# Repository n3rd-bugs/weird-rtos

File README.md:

Weird RTOS
==========
This is an educational RTOS that can be used with medium ended micro-controllers including 8-bit AVRs and Cortex-M3/4.

## Features
- Highly scalable for number of small to medium scale applications
- Priority based aperiodic scheduler
- Dynamic task creation and deletion
- *Condition* to create application specific signaling mechanisms like timers, events etc.
- *Semaphore* with optional specific interrupt protection
- *File system* based pipes to support data queues
- Support for suspending a single task on multiple conditions to eliminate multiple tasks
- A small networking stack with IPv4, ARP, UDP, TCP
- Support for idle work to offload low priority work from main tasks

## Supported MCUs and Platforms
| MCU/Platform | Core | RTOS Features |
| ------------ | ---- | -------- |
| atmega644 | AVR 8-bit | USART, ADC, SPI, Ethernet, MMC, File system, Alphanumeric LCD |
| atmega1284 | AVR 8-bit | USART, ADC, SPI, Ethernet, MMC, File system, Alphanumeric LCD |
| STM32F407vgt6 | Cortex-M4 | USART, SPI, Ethernet |
| STM32F103-stamp | Cortex-M3 | USART, ADC, SPI, Ethernet, MMC, File system, Alpha Numeric LCD |

## Minimum Requirements
| Controller | ROM | ROM actual\* | RAM | RAM Actual\*\* |
| ---------- | --- | ---------- | --- | ---------- |
| AVR 8-bit | 4 KB | 3086 bytes | 1 KB | 345 bytes |
| Cortex-M3 | 4 KB | 2075 bytes | 2 KB | 784 bytes |
| Cortex-M4 | 4 KB | 2139 bytes | 2 KB | 960 bytes |

_* with size optimizations_
_** hello.c example with serial disabled, not including system stack_

## Building
### Building as Library
To build the RTOS as library follow these steps:
1. Create a build folder
    `mkdir lib-build`
    `cd lib-build`
2. Configure the library project for a platform
    `cmake -G "Unix Makefiles" -DCMAKE_TOOLCHAIN_FILE=<path-to-root>/cmake/toolchains/<cross-tool>.cmake <path-to-root>`
3. Build the library
    `make`

The created library can be used to build sample applications using other tools.

### Building a Sample
To build an example project please follow these steps:
1. Create a build folder
    `mkdir build`
    `cd build`
2. Configure the example project for a platform
    `cmake -G "Unix Makefiles" -DCMAKE_TOOLCHAIN_FILE=<path-to-root>/cmake/toolchains/<cross-tool>.cmake <path-to-root>/examples/<example>`
3. Build the sample
    `make`

## Configurations
Weird-RTOS provides various configuration options that can be best viewed if project is configured through cmake-gui. These allow user to adjust various RTOS features according to his requirements.

## Source Organization

```
+-- 3rdparty - 3rd party components
+-- api - Higher level components including TFTP, weird-view IoT framework
+-- cmake - Cmake project files
|   +-- modules - Implements various helper APIs for cmake
|   +-- toolchains - Provides toolchain files
+-- docs - Related documentation
+-- examples - Some usage examples
+-- port - Target specific bits
|   +-- kernel - Target specific kernel components
|   +-- target - Platform specific device drivers
|       +-- <platform> - A platform entry
|           +-- board - Board specific configurations
|           +-- io - Device drivers
|           +-- schematics - Platform schematics if applicable
|           +-- utils - Broad utilities
|   +-- toolset - Toolset specific definitions
+-- rtos - Operating system generic components
|   +-- fs - File system
|   +-- io - IO device drivers and their middleware
|   +-- mem - Memory management
|   +-- net - Networking stack
|   +-- kernel - Kernel APIs
|   +-- utils - System utilities
```

## Documentation
### Kernel
- [Scheduler](docs/kernel/SCHEDULER.md)
- [Semaphore](docs/kernel/SEMAPHORE.md)
- [Sleep](docs/kernel/SLEEP.md)
- [Idle](docs/kernel/IDLE.md)
- [System Logging](docs/kernel/LOGGING.md)

## Licensing
This is a _non-commercial_ RTOS, for more details see [License Agreement](LICENSE.md).

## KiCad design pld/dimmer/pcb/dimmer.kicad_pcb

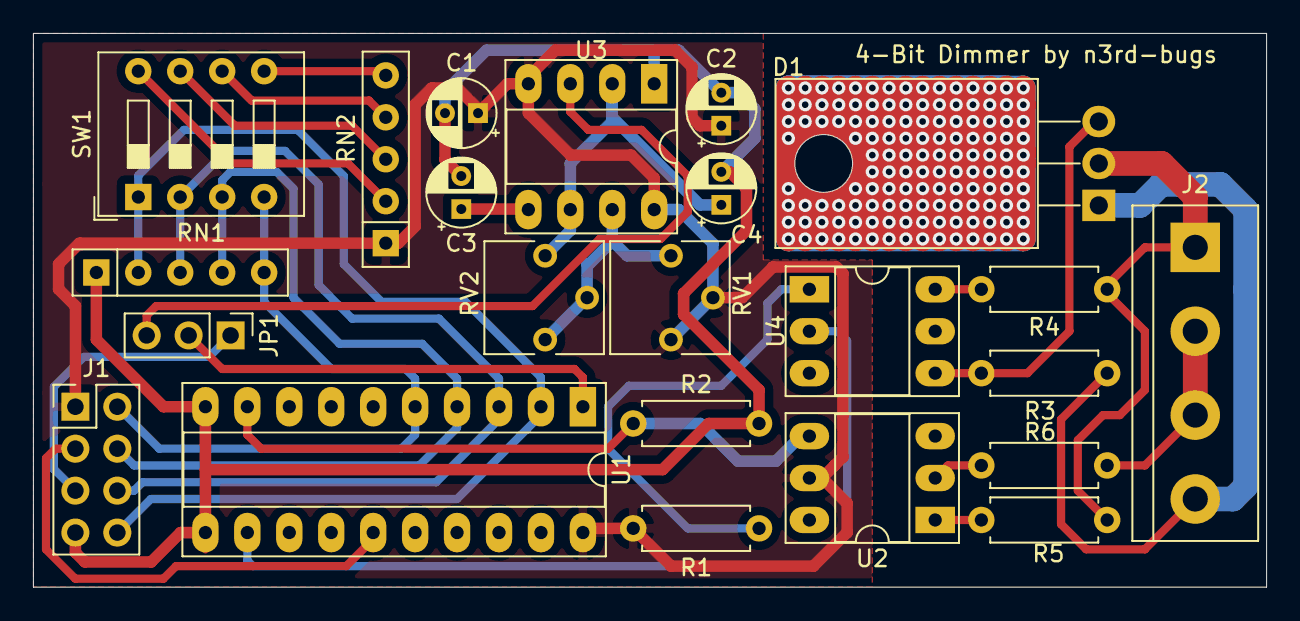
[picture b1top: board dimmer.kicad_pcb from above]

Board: 2 copper layers, 74.7 x 33.5 mm, 23 parts (0 on the bottom side), 27 nets.

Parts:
C1: .01u; CP_Radial_D4.0mm_P2.00mm
C2: 10u; CP_Radial_D4.0mm_P2.00mm
C3: 0.01u; CP_Radial_D4.0mm_P2.00mm
C4: ,1u; CP_Radial_D4.0mm_P2.00mm
D1: BTA20; TO-220-3_Horizontal_TabDown
J1: MCU; PinHeader_2x04_P2.54mm_Vertical
J2: AC/Load; TerminalBlock_bornier-4_P5.08mm
JP1: Jumper_3_Open; PinHeader_1x03_P2.54mm_Vertical
R1: 1k; R_Axial_DIN0207_L6.3mm_D2.5mm_P7.62mm_Horizontal
R2: 10k; R_Axial_DIN0207_L6.3mm_D2.5mm_P7.62mm_Horizontal
R3, R4: 100R; R_Axial_DIN0207_L6.3mm_D2.5mm_P7.62mm_Horizontal
R5, R6: 100k; R_Axial_DIN0207_L6.3mm_D2.5mm_P7.62mm_Horizontal
RN1: 10K; R_Array_SIP5
RN2: 100R; R_Array_SIP5
RV1, RV2: 10k; Potentiometer_Vishay_T73YP_Vertical
SW1: PWM; SW_DIP_SPSTx04_Slide_9.78x12.34mm_W7.62mm_P2.54mm
U1: GAL16V8; DIP-20_W7.62mm_Socket_LongPads
U2: 4N35; DIP-6_W7.62mm_Socket_LongPads
U3: LM555; DIP-8_W7.62mm_Socket_LongPads
U4: MOC3052M; DIP-6_W7.62mm_Socket_LongPads

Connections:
+5V: C1.1, C2.1, J1.1, R1.2, RN2.1, RV1.1, RV1.2, U1.20, U2.5, U3.4, U3.8
CLK: JP1.2, U1.1
CLK555: JP1.3, U3.3
CLKMCU: J1.5, JP1.1
GNDD: C1.2, C2.2, C3.2, C4.2, J1.7, R2.2, RN1.1, U1.10, U1.11, U3.1
IN-0: J1.8, RN1.2, SW1.1, U1.2
IN-1: J1.6, RN1.3, SW1.2, U1.3
IN-2: J1.4, RN1.4, SW1.3, U1.4
IN-3: J1.2, RN1.5, SW1.4, U1.5
LINEINV: J1.3, U1.15
Line: R2.1, U1.9, U2.4
unnamed: C3.1, U3.5
unnamed: C4.1, RV2.3, U3.2, U3.6
unnamed: D1.1, J2.4, R3.2
unnamed: D1.2, J2.1, R4.1, R5.2
unnamed: D1.3, R3.1, U4.4
unnamed: J2.2, J2.3, R6.1
unnamed: R1.1, U4.1
unnamed: R4.2, U4.6
unnamed: R5.1, U2.1
unnamed: R6.2, U2.2
unnamed: RN2.2, SW1.8
unnamed: RN2.3, SW1.7
unnamed: RN2.4, SW1.6
unnamed: RN2.5, SW1.5
unnamed: RV1.3, RV2.1, RV2.2, U3.7
TRIG: U1.12, U4.2

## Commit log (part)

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2017-08-04 Fixed LCD initialization failure.
2017-08-04 Moved cmake files in a seprate folder.
2017-08-04 Updated method of providing configuration.
2017-08-04 Added cmake configuration options for idle task.
2017-08-04 Added cmake configuration options for scheduler.
2017-08-04 Added configuration for smart switch over.
2017-08-06 Enabled WDT by default. Fixed milisec calculation.
2017-08-07 Renamed avr-gcc to avr8-gcc.
2017-08-07 Cosmetic updates.
2017-08-07 Fixed a build warning.
2017-08-07 Updated avr-gcc tools.
2017-08-07 Select target folder according to configuration.
2017-08-07 Fixed a build error.
2017-08-07 Adding cmake build system for stm32f407.
2017-08-07 Pick PLATFORM, CPU and TOOLs from cmake build system.
2017-08-07 Renamed avr8-gcc. Makde TGT_CPU hidden for AVR.
2017-08-07 Updated MCU to PLATFORM.
2017-08-07 Updated setup_config function.
2017-08-07 No need to force configuration if this is a tools file.
2017-08-07 Lets not build extra files.
2017-08-07 Renamed *_option.cmake files to *.cmake.
2017-08-07 Updated configuration with recent updates.
2017-08-07 Added PPP configurations.
2017-08-07 Added MMC configurations.
2017-08-07 Added enc28j60's configurations.
2017-08-07 Added file system configurations.
2017-08-07 Fixed a typo.
2017-08-08 Fixed typos.
2017-08-08 Fixed various typos.
2017-08-08 Updated default configurations.
2017-08-09 Updated cmake helper.
2017-08-09 Added configurations for utils.
2017-08-09 Updated default ADC configuration.
2017-08-09 Added configurations for AVR I2C driver.
2017-08-09 Added configurations for AVR USART driver.
2017-08-10 Integarted expected value API in the configuration function. Added a value map function.
2017-08-10 Updated AVR project.
2017-08-10 Added configurations for AVR LCD.
2017-08-10 Updated ENC28J60 device configurations for AVR.
2017-08-10 Lets not show extra options.
2017-08-10 Updated smart change over project for 16MHz.
2017-08-13 Updated AVR project configurations.
2017-08-13 Revert "Updated smart change over project for 16MHz."
    This reverts commit b4757ce32d933f22177a2443aec9a9275bf533ff.
2017-08-13 Lets not drive the IO low when sending low signal to remote.
2017-08-19 Added configuration options for STM32F407.
2017-08-19 Updated smart change over demo with new updates.
2017-08-19 Bumped the release version.
2017-09-04 Fixed build error for serial.
2017-09-04 Added configurations for AVR bootloader.
2017-09-15 Fixed a build error if NET is disabled.
2017-09-15 Updated atmega644 to atmegaxx4.
2017-09-15 Moved platform configuration to the port root.
2017-09-17 Adding OLED driver for AVR.
2017-09-17 Added OLED example.
2017-09-24 Updated examples.
2017-09-24 AVR dude configuration should be platform specific.
2017-09-30 Removed OLED configuration.
2017-10-01 Removed unused variables from linker script.
2017-10-07 Adding openOCD configuration for STM32F407.
2017-10-07 Updated ISR managment for STM32F407.
2017-10-07 Do not set TX complete flag.
2017-10-07 Updated default boudrate.
2017-10-07 Disable other interrupts when invoking context switch.
2017-10-07 Made interrupt flag volatile.
2017-10-14 Fixed sysinfo messages.
2017-10-14 On some platforms HW ticks may overflow in uint32_t type.
2017-10-14 Added heap memory in stm32f407.
2017-10-14 Use nano specs for STM32 platforms.
2017-10-14 Added hardware ticks per second macro for STM32F103.
2017-10-14 Added a new error code.
2017-10-14 Added OLED driver for STM32.
2017-10-28 Updated license for weird-rtos.
2017-10-28 Updated CONFIG_TASK_* configurations with TASK_*.
2017-10-28 Removed extra code from cortex-m4.
2017-10-28 Updated serial driver to not block on space if it is buffered.
2017-10-28 Pick the larger value when calculating baud scale.
2017-10-28 Added target heap configurations.
2017-10-28 Wait for the requried number of buffers before allocating them.
2017-10-28 Fixed a buffer leak from fs_puts.
2017-10-28 Fixed a comment.
2017-10-28 Adding support for SPI in stm32f103.
2017-10-28 Adding enc28j60 driver for stm32f103.
2017-11-05 Adding support for SP2.
2017-11-05 Adding MMC/SD base for STM32F103.
2017-11-12 Updated build flags.
2017-11-12 Updated SPI driver for STM32F407 platform.
2017-11-15 Fixed PPP cmake build.
2017-11-15 Updated enc28j60 driver for STM32F103 to free the USART2 line.
2017-11-15 Removed an target specific definition.
2017-11-21 Added separate clocks of APB1/APB2.
2017-11-21 Adding support for USART3.
2017-11-21 Adding PPP base for STM32F103.
2017-11-21 Moved PA0/PA1 to PB0/PB1 to free up USART signals.
2017-11-22 Updated number of buffers reserved for PPP.
2017-11-24 Moved AVR specific definitions in AVR port.
2017-11-24 Updated ENC28J60 for STM32F103 to use PC14/15 for INT/RST.
2017-11-26 Updated README for new stable.
2017-12-01 Adding support in file buffer to copy data from one buffer to another.
2017-12-02 Make a copy of a frame if we need to return this frame to stack.
2017-12-03 Fixed a buffer corruption.
2017-12-03 Fixed a semaphore inversion.
2017-12-03 Release the TCP port lock when re-transmiting a frame.
2017-12-09 Couple of more bug fixes.
2017-12-10 Fixed a data exception.
2017-12-25 Try resume for the condition we resumed from first.
2017-12-28 Fixed buffer leaks from PPP.
2017-12-28 Removed support for connected files.
2017-12-28 Renamed FS_BUFFER to FS_BUFFER_LIST and FS_BUFFER_ONE to FS_BUFFER.
2017-12-31 Adding build configuration to enable or disable DHCP client.
2018-01-02 Moved status to suspend as it is something that will be retained even after a condition is deleted.
2018-01-02 Updated net work queue to pass around positive status and convert it to a negative status when retruning to the caller.
2018-01-07 Fixed static variable deceleration.
2018-01-07 Adding DHCP configuration file.
2018-02-24 Added support for separate configuration files.
2018-02-24 Separated configuration files for various components.
2018-02-24 Added configuration options for INT and RST pins for atmegaxx4.
2018-02-24 We should return 0 bytes if there is no data availabe to read.
2018-02-24 Should to try to access the debug descriptor if it is not yet initialized.
2018-02-24 No need to pass FS_BUFFER_HEAD to push API.
2018-02-24 No need to cast pointer to an integer.
2018-02-24 Fixed linker flag manipulation for AVR.
2018-02-24 Fixed build if toolchain path has a space in it.
2018-02-24 Print the current task in case of a system crash.
2018-02-24 Read the character before manipulaating buffer.
2018-02-24 Revamped AVR USART driver. Added support for multiple devices. Added support for external hardware flow control.
2018-02-24 Reading RTS feedback sometimes end up in a lock if data starts to RX immediately.
2018-02-24 Fixed an unwanted PPP control packet transmission.
2018-02-24 Show read progress, fixed read for > 0x10000 address.
2018-02-24 Added support for PPP in atmega.
2018-02-25 Cosmetic updates, fixed indentation.
2018-03-03 Updated bootloader
    It was seen that if user tries to overwrite the bootloader section the
    target becomes unusable.
    To avoid this situation added checks to not overwrite the bootloader
    section.
    Made entry point for bootloader loaded/nonloader applications identical.
    Fixed offset/size calculation.
2018-03-03 Delay RTS reset
    Added a delay in RTS reset to aviod unwanted RTS recovery.
2018-07-15 Fixed ENC28J60 INT PIN default configuration.
2018-08-05 Updated smart change over demo to reset the LCD interface on each cycle.
2019-02-09 Adding avrdude target for atmega1284 even if bootloader if disabled.
2019-02-09 Adding support in enc28j60 to drop partial frames.
2019-02-09 Fixed enc28j60 build with interrupt polling disabled.
2019-02-09 Updated ADC reading sampling.
2019-02-09 Reset LCD interface after each cycle to workaround LCD hang issue.
2019-02-09 Added configuration to pass fames with mismatched length at IPv4 layer.
2019-02-09 Added configuration to pass fames with mismatched length at UDP layer.
2019-02-09 Minor updates.
2019-12-02 Fixed inline build for SLL.
2019-12-13 Removing various white spaces.
2019-12-18 Created .gitattributes
2019-12-21 Ignore pyc files.
2019-12-24 Updated setup_env_win with new paths.
2019-12-24 Updated sys log.
    Updated SYS_LOG_NONE to SYS_LOG_ENABLE.
    Removed printf where possible.
2019-12-24 Added ultoa_b10 to replace snprintf.
2019-12-24 Updated current_timeout to uint32_t from uint16_t
2019-12-24 Updated sys_info to not use snprintf.
    More information in sys_info.
2019-12-24 Adding stub for PROGMEM
2019-12-24 Updated AVR port
    Updated list of supported MCUs.
    Updated kernel integration as required by new updates.
    Added linker scripts for the MCUs supporting bootloader.
2019-12-24 Fixed build for SPI_BB.
2019-12-24 Updated bootloader for AVR
    Added a README.md.
    Cosmetic updates.
2019-12-24 Added code for arduino-isp
2019-12-24 Updated port for cortex-m3 and cortex-m4
2019-12-24 Adding initial port for stm32f411
2019-12-24 Renamed stm32f407.ld to stm32f407vgt6.ld
2019-12-24 Renamed stm32f4discovery to stm32f4vgt6
2019-12-24 Updated STM32F407 discovery port
    Updated ISR table.
    Removed extra definitions.
    Cosmetic updates.
2019-12-24 Updated target names in build system.
2019-12-24 Updated werid view server demo as per new updates.
2019-12-24 Adding initial version of incubator.
2019-12-26 More clean up of sleep less system.
2019-12-27 Updated STM32F030 to use PA2/PA3 for USART.
2019-12-27 Cosmetic updates in STM32F103 I2C driver.
2019-12-30 Fixed couple of bugs in I2C interface,
2019-12-30 Clear display during initialization.
2019-12-30 Removing white line after the file header.
2019-12-31 Adding base for graphics interface.
2019-12-31 Making the file name const.
2019-12-31 Removing LCD_AN_DEBUG configuration,
2019-12-31 Use io_puts for syslog.
2019-12-31 Use buffer IO. seems like even calling the IO APIs make the STD lib functions to become part of image.
2020-01-01 Reset the tick_sleep when a task is removed from the sleeping tasks list.
2020-01-03 Adding driver for DHTXX devices.
2020-01-03 Fixed BSS initilization for stm32f030.
2020-01-03 USer timer 3 for HW tick.
2020-01-06 Stabilized DHTXX driver.
2020-01-06 Dimmer on 16v8.
2020-01-11 Updated smart chage over to use larger buffer size to optimiza data section
2020-01-14 Removing CMAKE_BUILD macro
    Removed CMAKE_BUILD macro, only building a cmake generated project will be supported by default.
2020-01-14 Restructured GPIO drivers.
2020-01-16 Stashing changes so far.
2020-01-16 Updated mension of LCD on its own to Alphanumeric LCD
2020-01-17 Fixed oled build for stm32f103
2020-01-17 Added max7219 subsytem.
2020-01-17 Hooked up GFX interface.
2020-01-17 Bug fixes and testing.
2020-01-27 Updated device name to led8x8
2020-01-30 Fixed serail hang issue incase of data overrun for STM32F030
2020-01-30 Added handling of rest of the NMEA messages.
2020-01-30 Cosmetic updates
2020-01-31 Added API to flush RX data from a file descriptor.
2020-02-04 Wrapping up NMEA updates.
2020-02-04 Adding base for dimmer pcb
2020-02-04 Schematics clean-up
2020-02-04 Added initial version of PCB
2020-02-04 Moved the files in a new folder
2020-02-04 Updated schematics for dimmer
2020-02-05 Fixed parsing of values in NMEA.
2020-02-06 Adding ENC28J60 driver for STM32F411
2020-02-10 For IO components use IO_XXX scheme in configuration.
2020-02-11 Adding ADC support for stm32f030
2020-03-13 Updated PCB with latest changes.
2020-05-06 Fixing build error if LCD_AN is enabled.
2020-05-06 Updated syslog to flush the STDOUT if buffer IO is being used.
2020-05-14 Swicth off the generator relay before turing off the the generator.
    Swicth off the generator relay before turing off the the generator.
    Updated various variable names as per new design.
